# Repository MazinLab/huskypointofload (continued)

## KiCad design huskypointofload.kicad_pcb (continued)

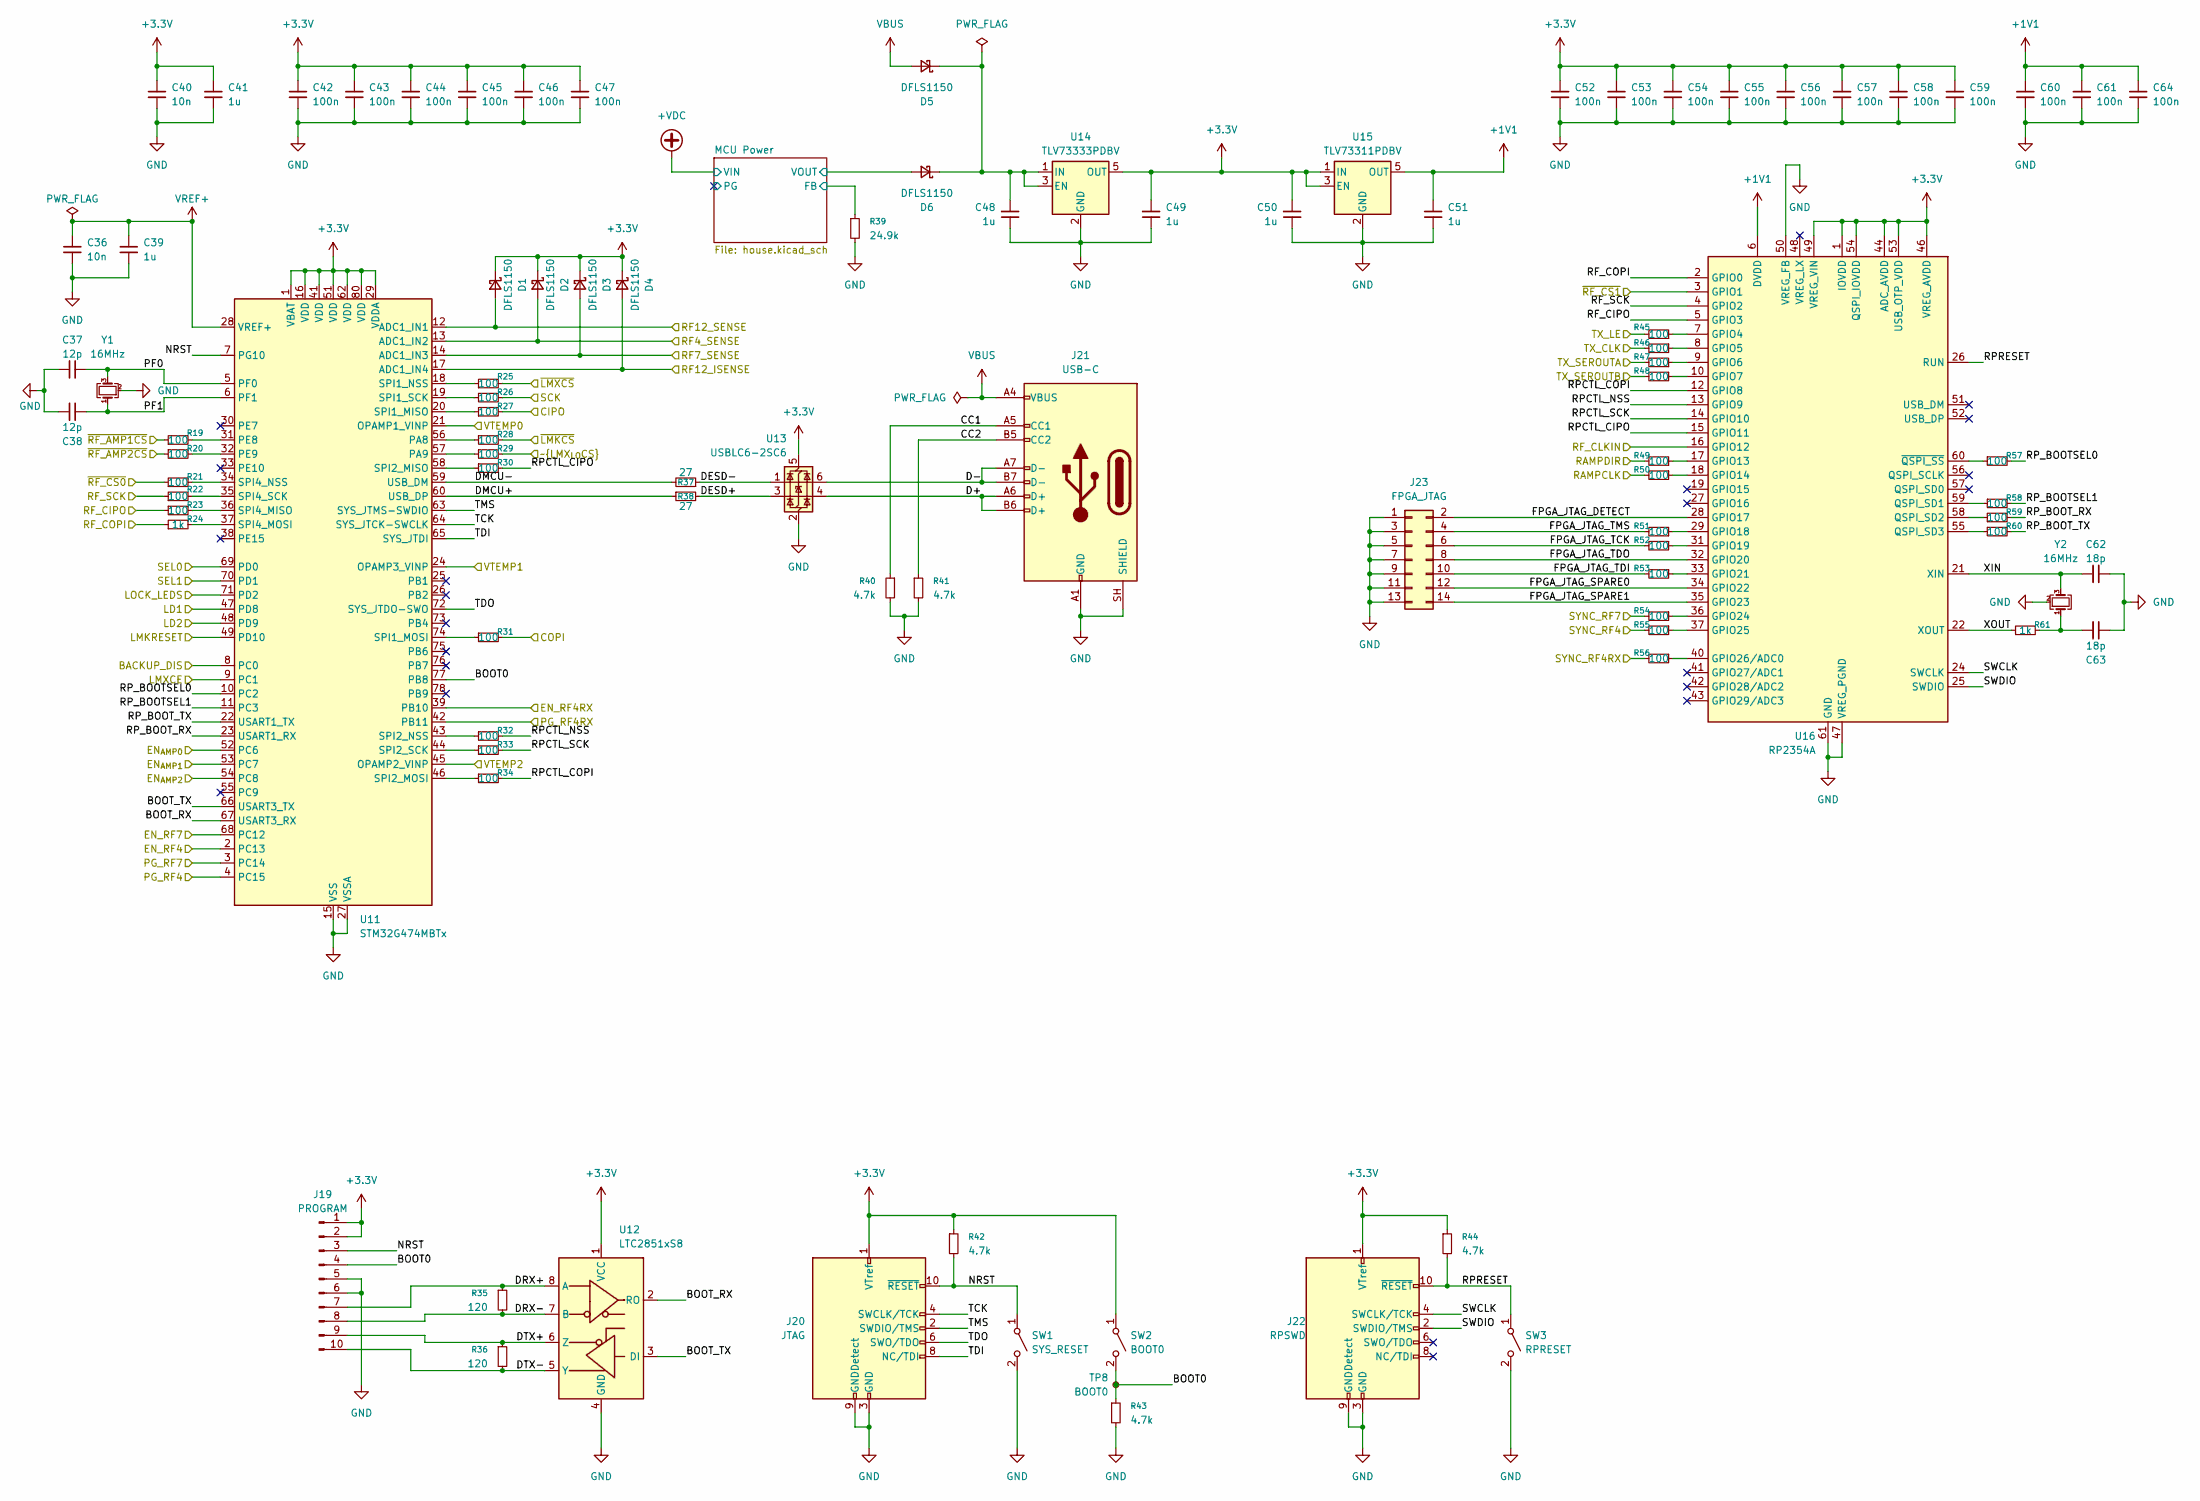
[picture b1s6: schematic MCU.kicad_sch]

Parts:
C36, C40: 10n; C_0402_1005Metric; DIGIKEY_PN 490-6351-1-ND
C37, C38: 12p; C_0402_1005Metric; DIGIKEY_PN 490-11190-1-ND
C39, C41: 1u; C_0402_1005Metric; DIGIKEY_PN 490-13339-1-ND
C42, C43, C44, C45, C46, C47, C52, C53, C54, C55, C56, C57, C58, C59, C60, C61, C64: 100n; C_0402_1005Metric; DIGIKEY_PN 490-14603-1-ND
C48, C49, C50, C51: 1u; C_0402_1005Metric
C62, C63: 18p; C_0402_1005Metric
D1, D2, D3, D4, D5, D6: DFLS1150; D_PowerDI-123; DIGIKEY_PN DFLS1150DICT-ND
J19: PROGRAM; Molex_PicoBlade_53048-1010_1x10_P1.25mm_Horizontal
J20: JTAG; PinHeader_2x05_P1.27mm_Vertical_SMD; DIGIKEY_PN SAM1161-05-ND
J21: USB-C; USB_C_Receptacle_JAE_DX07S016JA1R1500; DIGIKEY_PN 670-DX07S016JA1R1500CT-ND
J22: RPSWD; PinHeader_2x05_P1.27mm_Vertical_SMD; DIGIKEY_PN SAM1161-05-ND
J23: FPGA_JTAG
R19, R20, R21, R22, R23, R25, R26, R27, R28, R29, R30, R31, R32, R33, R34, R45, R46, R47, R48, R49, R50, R51, R52, R53, R54, R55, R56, R57, R58, R59, R60: 100; R_0402_1005Metric
R24, R61: 1k; R_0402_1005Metric
R35, R36: 120; R_0402_1005Metric; DIGIKEY_PN 311-120LRCT-ND
R37, R38: 27; R_0402_1005Metric; DIGIKEY_PN P27.0LCT-ND
R39: 24.9k; R_0402_1005Metric
R40, R41, R42, R43, R44: 4.7k; R_0402_1005Metric; DIGIKEY_PN 311-4.7KJRCT-ND
SW1: SYS_RESET; SW_SPST_PTS810; DIGIKEY_PN CKN10502CT-ND
SW2: BOOT0; SW_SPST_PTS810; DIGIKEY_PN CKN10502CT-ND
SW3: RPRESET; SW_SPST_PTS810; DIGIKEY_PN CKN10502CT-ND
TP8: BOOT0; TestPoint_Keystone_5015_Micro_Mini; DIGIKEY_PN 36-5015CT-ND
U11: STM32G474MBTx; LQFP-80_12x12mm_P0.5mm; DIGIKEY_PN 497-STM32G474MBT6-ND
U12: LTC2851xS8; SOIC-8_3.9x4.9mm_P1.27mm; DIGIKEY_PN LTC2851IMS8#TRPBFCT-ND
U13: USBLC6-2SC6; SOT-23-6; DIGIKEY_PN 4518-USBLC6-2SC6CT-ND
U14: TLV73333PDBV; SOT-23-5
U15: TLV73311PDBV; SOT-23-5
U16: RP2354A; QFN-60-1EP_7x7mm_P0.4mm_EP3.4x3.4mm
Y1, Y2: 16MHz; Crystal_SMD_3225-4Pin_3.2x2.5mm_HandSoldering; DIGIKEY_PN 2151-RH100-16.000-8-2020-TRCT-ND

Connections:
+1V1: C51.1, C60.1, C61.1, C64.1, U15.5 (OUT), U16.6 (DVDD), U16.23 (DVDD), U16.39 (DVDD)
+3.3V: C40.1, C41.1, C42.1, C43.1, C44.1, C45.1, C46.1, C47.1, C49.1, C50.1, C52.1, C53.1, C54.1, C55.1, C56.1, C57.1, C58.1, C59.1, D1.1 (K), D2.1 (K), D3.1 (K), D4.1 (K), J19.1, J19.2, J20.1 (VTref), J22.1 (VTref), R42.1, R44.1, SW2.1 (A), U11.1 (VBAT), U11.16 (VDD), U11.29 (VDDA), U11.41 (VDD), U11.51 (VDD), U11.62 (VDD), U11.80 (VDD), U12.1 (VCC), U13.5 (VBUS), U14.5 (OUT), U15.1 (IN), U15.3 (EN), U16.1 (IOVDD), U16.11 (IOVDD), U16.20 (IOVDD), U16.30 (IOVDD), U16.38 (IOVDD), U16.44 (ADC_AVDD), U16.45 (IOVDD), U16.46 (VREG_AVDD), U16.49 (VREG_VIN), U16.53 (USB_OTP_VDD), U16.54 (QSPI_IOVDD); also elsewhere on the board
/Clocking/BACKUP_DIS: U11.8 (PC0); also elsewhere on the board
/Clocking/LD1: U11.47 (PD8); also elsewhere on the board
/Clocking/LD2: U11.48 (PD9); also elsewhere on the board
/Clocking/LD_LED_ENABLE: U11.71 (PD2); also elsewhere on the board
/Clocking/LMK04828/SEL0: U11.69 (PD0); also elsewhere on the board
/Clocking/LMK04828/SEL1: U11.70 (PD1); also elsewhere on the board
/Clocking/LMKRESET: U11.49 (PD10); also elsewhere on the board
/Clocking/LMXCE: U11.9 (PC1); also elsewhere on the board
/Clocking/MUXOUT: R27.2; also elsewhere on the board
/Clocking/RAMPCLK: R50.2; also elsewhere on the board
/Clocking/RAMPDIR: R49.2; also elsewhere on the board
/Clocking/~LMKCS: R28.2; also elsewhere on the board
/Clocking/~LMXCS: R25.2; also elsewhere on the board
/Clocking/~LMX_{LOCS}: R29.2; also elsewhere on the board
/MCU/BOOT0: J19.4, R43.1, SW2.2 (B), TP8.1 (1_1), U11.77 (PB8)
/MCU/BOOT_RX: U11.67 (USART3_RX), U12.2 (RO)
/MCU/BOOT_TX: U11.66 (USART3_TX), U12.3 (DI)
/MCU/CC1: J21.A5 (CC1), R40.1
/MCU/CC2: J21.B5 (CC2), R41.1
/MCU/D+: J21.A6 (D+), J21.B6 (D+), U13.4 (I/O2)
/MCU/D-: J21.A7 (D-), J21.B7 (D-), U13.6 (I/O1)
/MCU/DESD+: R38.2, U13.3 (I/O2)
/MCU/DESD-: R37.1, U13.1 (I/O1)
/MCU/DMCU+: R38.1, U11.60 (USB_DP)
/MCU/DMCU-: R37.2, U11.59 (USB_DM)
/MCU/DRX+: J19.7, R35.1, U12.8 (A)
/MCU/DRX-: J19.8, R35.2, U12.7 (B)
/MCU/DTX+: J19.9, R36.1, U12.6 (Z)
/MCU/DTX-: J19.10, R36.2, U12.5 (Y)
/MCU/EN_RF4: U11.2 (PC13); also elsewhere on the board
/MCU/EN_RF4RX: U11.39 (PB10); also elsewhere on the board
/MCU/EN_RF7: U11.68 (PC12); also elsewhere on the board
/MCU/EN_{AMP0}: U11.52 (PC6); also elsewhere on the board
/MCU/EN_{AMP1}: U11.53 (PC7); also elsewhere on the board
/MCU/EN_{AMP2}: U11.54 (PC8); also elsewhere on the board
/MCU/FPGA_JTAG_DETECT: J23.2, U16.28 (GPIO17)
/MCU/FPGA_JTAG_SPARE0: J23.12, U16.34 (GPIO22)
/MCU/FPGA_JTAG_SPARE1: J23.14, U16.35 (GPIO23)
/MCU/FPGA_JTAG_TCK: J23.6, R52.2
/MCU/FPGA_JTAG_TDI: J23.10, R53.2
/MCU/FPGA_JTAG_TDO: J23.8, U16.32 (GPIO20)
/MCU/FPGA_JTAG_TMS: J23.4, R51.2
/MCU/MCU Power/FB: R39.1; also elsewhere on the board
/MCU/MCU Power/VOUT: D6.2 (A); also elsewhere on the board
/MCU/NRST: J19.3, J20.10 (~RESET), R42.2, SW1.1 (A), U11.7 (PG10)
/MCU/PF0: C37.2, U11.5 (PF0), Y1.3
/MCU/PF1: C38.2, U11.6 (PF1), Y1.1
/MCU/PG_RF4: U11.4 (PC15); also elsewhere on the board
/MCU/PG_RF4RX: U11.42 (PB11); also elsewhere on the board
/MCU/PG_RF7: U11.3 (PC14); also elsewhere on the board
/MCU/RF4_SENSE: D2.2 (A), U11.13 (ADC1_IN2); also elsewhere on the board
/MCU/RF7_SENSE: D3.2 (A), U11.14 (ADC1_IN3); also elsewhere on the board
/MCU/RF12_ISENSE: D4.2 (A), U11.17 (ADC1_IN4); also elsewhere on the board
/MCU/RF12_SENSE: D1.2 (A), U11.12 (ADC1_IN1); also elsewhere on the board
/MCU/RF_CLKIN: U16.16 (GPIO12); also elsewhere on the board
/MCU/RPCTL_CIPO: R30.2, U16.15 (GPIO11)
/MCU/RPCTL_COPI: R34.2, U16.12 (GPIO8)
/MCU/RPCTL_NSS: R32.2, U16.13 (GPIO9)
/MCU/RPCTL_SCK: R33.2, U16.14 (GPIO10)
/MCU/RPRESET: J22.10 (~RESET), R44.2, SW3.1 (A), U16.26 (RUN)
/MCU/RP_BOOTSEL0: R57.2, U11.10 (PC2)
/MCU/RP_BOOTSEL1: R58.2, U11.11 (PC3)
/MCU/RP_BOOT_RX: R59.2, U11.23 (USART1_RX)
/MCU/RP_BOOT_TX: R60.2, U11.22 (USART1_TX)
/MCU/SWCLK: J22.4 (SWCLK/TCK), U16.24 (SWCLK)
/MCU/SWDIO: J22.2 (SWDIO/TMS), U16.25 (SWDIO)
/MCU/SYNC_RF4: R55.2; also elsewhere on the board
/MCU/SYNC_RF4RX: R56.2; also elsewhere on the board
/MCU/SYNC_RF7: R54.2; also elsewhere on the board
/MCU/TCK: J20.4 (SWCLK/TCK), U11.64 (SYS_JTCK-SWCLK)
/MCU/TDI: J20.8 (NC/TDI), U11.65 (SYS_JTDI)
/MCU/TDO: J20.6 (SWO/TDO), U11.72 (SYS_JTDO-SWO)
/MCU/TMS: J20.2 (SWDIO/TMS), U11.63 (SYS_JTMS-SWDIO)
/MCU/TX_SEROUTA: R47.2; also elsewhere on the board
/MCU/TX_SEROUTB: R48.2; also elsewhere on the board
/MCU/VTEMP0: U11.21 (OPAMP1_VINP); also elsewhere on the board
/MCU/VTEMP1: U11.24 (OPAMP3_VINP); also elsewhere on the board
/MCU/VTEMP2: U11.45 (OPAMP2_VINP); also elsewhere on the board
/MCU/XIN: C62.2, U16.21 (XIN), Y2.3
/MCU/XOUT: R61.1, U16.22 (XOUT)
/RF_CIPO: R23.1, U16.5 (GPIO3); also elsewhere on the board
/RF_COPI: R24.1, U16.2 (GPIO0); also elsewhere on the board
/RF_SCK: R22.1, U16.4 (GPIO2); also elsewhere on the board
/Recieve Chain/CIPO: R31.2; also elsewhere on the board
/Recieve Chain/SCK: R26.2; also elsewhere on the board
/Recieve Chain/~CS_{AMP1}: R19.1; also elsewhere on the board
/Recieve Chain/~CS_{AMP2}: R20.1; also elsewhere on the board
/Transmit Chain/CLK: R46.2; also elsewhere on the board
/Transmit Chain/LE: R45.2; also elsewhere on the board
/~RF_CS0: R21.1; also elsewhere on the board
/~RF_CS1: U16.3 (GPIO1); also elsewhere on the board
GND: C36.2, C37.1, C38.1, C39.2, C40.2, C41.2, C42.2, C43.2, C44.2, C45.2, C46.2, C47.2, C48.2, C49.2, C50.2, C51.2, C52.2, C53.2, C54.2, C55.2, C56.2, C57.2, C58.2, C59.2, C60.2, C61.2, C62.1, C63.1, C64.2, J19.5, J19.6, J20.3 (GND), J20.5 (GND), J20.9 (GNDDetect), J21.A1 (GND), J21.A12 (GND), J21.B1 (GND), J21.B12 (GND), J21.SH (SHIELD), J22.3 (GND), J22.5 (GND), J22.9 (GNDDetect), J23.1, J23.3, J23.5, J23.7, J23.9, J23.11, J23.13, R39.2, R40.2, R41.2, R43.2, SW1.2 (B), SW3.2 (B), U11.15 (VSS), U11.27 (VSSA), U11.40 (VSS), U11.50 (VSS), U11.61 (VSS), U11.79 (VSS), U12.4 (GND), U13.2 (GND), U14.2 (GND), U15.2 (GND), U16.47 (VREG_PGND), U16.50 (VREG_FB), U16.61 (GND), Y1.2 (G), Y1.4 (G), Y2.2 (G), Y2.4 (G); also elsewhere on the board
unnamed: C63.2, R61.2, Y2.1
unnamed: C48.1, D5.1 (K), D6.1 (K), U14.1 (IN), U14.3 (EN)
unnamed: R25.1, U11.18 (SPI1_NSS)
unnamed: R26.1, U11.19 (SPI1_SCK)
unnamed: R27.1, U11.20 (SPI1_MISO)
unnamed: R28.1, U11.56 (PA8)
unnamed: R29.1, U11.57 (PA9)
unnamed: R30.1, U11.58 (SPI2_MISO)
unnamed: R31.1, U11.74 (SPI1_MOSI)
unnamed: R32.1, U11.43 (SPI2_NSS)
unnamed: R33.1, U11.44 (SPI2_SCK)
unnamed: R34.1, U11.46 (SPI2_MOSI)
unnamed: R19.2, U11.31 (PE8)
unnamed: R20.2, U11.32 (PE9)
unnamed: R21.2, U11.34 (SPI4_NSS)
unnamed: R22.2, U11.35 (SPI4_SCK)
unnamed: R23.2, U11.36 (SPI4_MISO)
unnamed: R24.2, U11.37 (SPI4_MOSI)
unnamed: R45.1, U16.7 (GPIO4)
unnamed: R46.1, U16.8 (GPIO5)
unnamed: R47.1, U16.9 (GPIO6)
unnamed: R48.1, U16.10 (GPIO7)
unnamed: R49.1, U16.17 (GPIO13)
unnamed: R50.1, U16.18 (GPIO14)
unnamed: R51.1, U16.29 (GPIO18)
unnamed: R52.1, U16.31 (GPIO19)
unnamed: R53.1, U16.33 (GPIO21)
unnamed: R54.1, U16.36 (GPIO24)
unnamed: R55.1, U16.37 (GPIO25)
unnamed: R56.1, U16.40 (GPIO26/ADC0)
unnamed: R58.1, U16.59 (QSPI_SD1)
unnamed: R59.1, U16.58 (QSPI_SD2)
unnamed: R60.1, U16.55 (QSPI_SD3)
unnamed: R57.1, U16.60 (~QSPI_SS)
VBUS: D5.2 (A), J21.A4 (VBUS), J21.A9 (VBUS), J21.B4 (VBUS), J21.B9 (VBUS)
VREF+: C36.1, C39.1, U11.28 (VREF+)

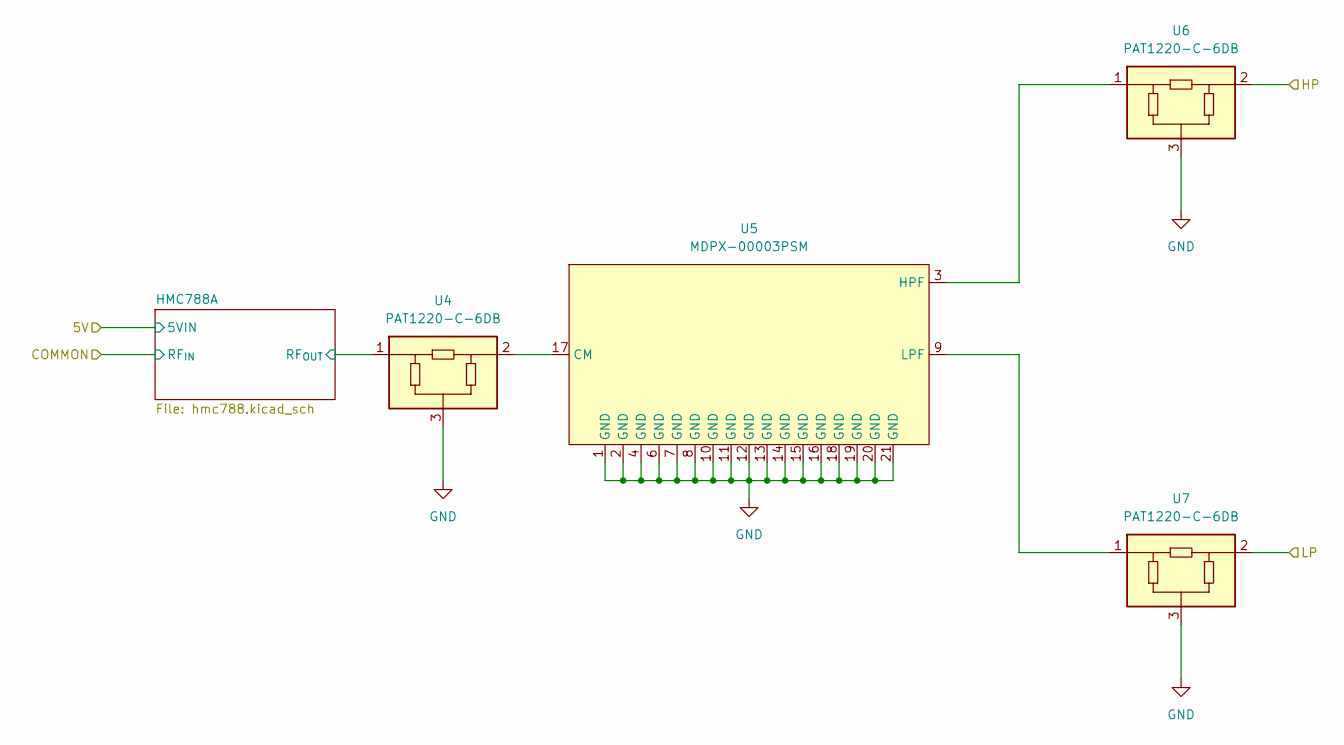
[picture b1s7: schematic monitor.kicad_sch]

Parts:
U4, U6, U7: PAT1220-C-6DB; RF_Attenuator_Susumu_PAT1220
U5: MDPX-00003PSM; VQFN-24-1EP_4x4mm_P0.5mm_EP2.45x2.45mm

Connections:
/Monitor Path/HMC788A/RF_{OUT}: U4.1; also elsewhere on the board
/Monitor Path/HP: U6.2; also elsewhere on the board
/Monitor Path/LP: U7.2; also elsewhere on the board
GND: U4.3, U5.1 (GND), U5.2 (GND), U5.4 (GND), U5.6 (GND), U5.7 (GND), U5.8 (GND), U5.10 (GND), U5.11 (GND), U5.12 (GND), U5.13 (GND), U5.14 (GND), U5.15 (GND), U5.16 (GND), U5.18 (GND), U5.19 (GND), U5.20 (GND), U5.21 (GND), U6.3, U7.3; also elsewhere on the board
unnamed: U4.2, U5.17 (CM)
unnamed: U5.3 (HPF), U6.1
unnamed: U5.9 (LPF), U7.1

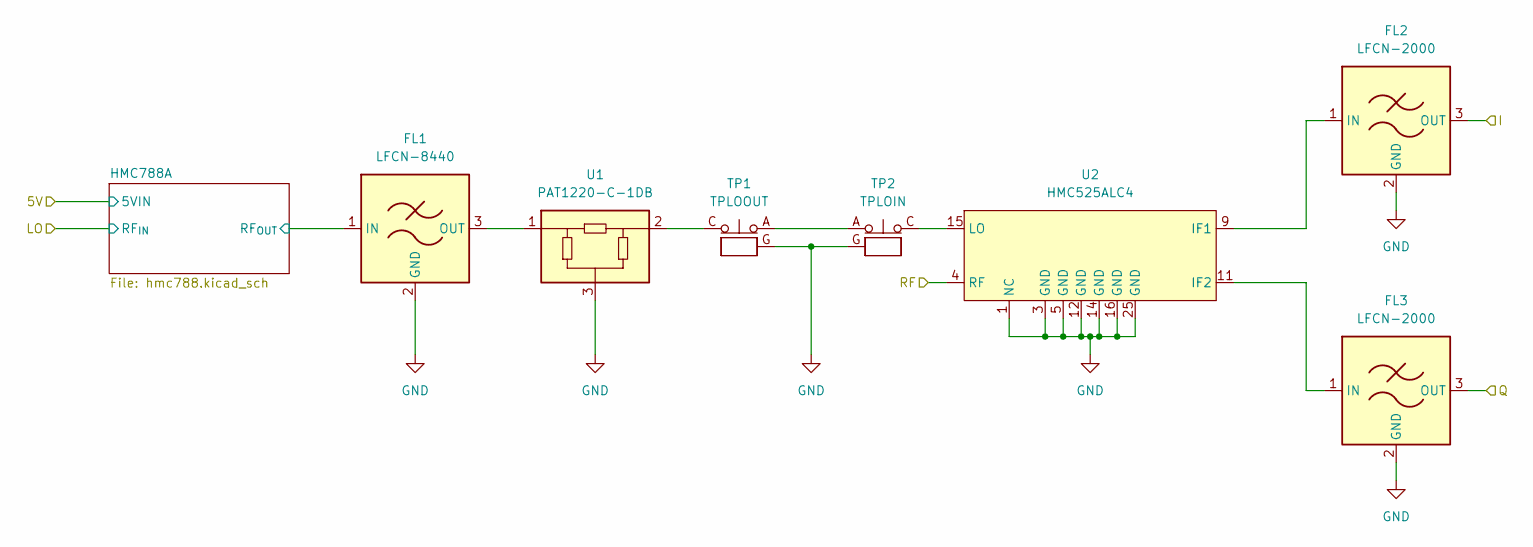
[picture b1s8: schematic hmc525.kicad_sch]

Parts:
FL1: LFCN-8440; Filter_Mini-Circuits_FV1206-4
FL2, FL3: LFCN-2000; Filter_Mini-Circuits_FV1206
TP1: TPLOOUT; CoaxialSwitch_Hirose_MS-156C3_Horizontal
TP2: TPLOIN; CoaxialSwitch_Hirose_MS-156C3_Horizontal
U1: PAT1220-C-1DB; RF_Attenuator_Susumu_PAT1220
U2: HMC525ALC4; QFN-24-1EP_4x4mm_P0.5mm_EP2.5x2.5mm

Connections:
/TX Mixer/HMC788A/RF_{OUT}: FL1.1 (IN); also elsewhere on the board
/TX Mixer/I: FL2.3 (OUT); also elsewhere on the board
/TX Mixer/Q: FL3.3 (OUT); also elsewhere on the board
/TX Mixer/RF: U2.4 (RF); also elsewhere on the board
GND: FL1.2 (GND), FL1.4 (GND), FL2.2 (GND), FL2.4 (GND), FL3.2 (GND), FL3.4 (GND), TP1.G, TP2.G, U1.3, U2.1 (NC), U2.2 (NC), U2.3 (GND), U2.5 (GND), U2.6 (NC), U2.7 (NC), U2.8 (NC), U2.10 (NC), U2.12 (GND), U2.13 (NC), U2.14 (GND), U2.16 (GND), U2.17 (NC), U2.18 (NC), U2.19 (NC), U2.20 (NC), U2.21 (NC), U2.22 (NC), U2.23 (NC), U2.24 (NC), U2.25 (GND); also elsewhere on the board
unnamed: FL1.3 (OUT), U1.1
unnamed: FL2.1 (IN), U2.9 (IF1)
unnamed: FL3.1 (IN), U2.11 (IF2)
unnamed: TP1.A, TP2.A
unnamed: TP1.C, U1.2
unnamed: TP2.C, U2.15 (LO)

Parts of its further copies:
FL4: LFCN-8440; Filter_Mini-Circuits_FV1206-4
FL5, FL6: LFCN-2000; Filter_Mini-Circuits_FV1206
TP19: TPLOOUT; CoaxialSwitch_Hirose_MS-156C3_Horizontal
TP20: TPLOIN; CoaxialSwitch_Hirose_MS-156C3_Horizontal
U42: PAT1220-C-1DB; RF_Attenuator_Susumu_PAT1220
U43: HMC525ALC4; QFN-24-1EP_4x4mm_P0.5mm_EP2.5x2.5mm

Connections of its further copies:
/RX Mixer/HMC788A/RF_{OUT}: FL4.1 (IN); also elsewhere on the board
/RX Mixer/I: FL5.3 (OUT); also elsewhere on the board
/RX Mixer/Q: FL6.3 (OUT); also elsewhere on the board
/RX Mixer/RF: U43.4 (RF); also elsewhere on the board
GND: FL4.2 (GND), FL4.4 (GND), FL5.2 (GND), FL5.4 (GND), FL6.2 (GND), FL6.4 (GND), TP19.G, TP20.G, U42.3, U43.1 (NC), U43.2 (NC), U43.3 (GND), U43.5 (GND), U43.6 (NC), U43.7 (NC), U43.8 (NC), U43.10 (NC), U43.12 (GND), U43.13 (NC), U43.14 (GND), U43.16 (GND), U43.17 (NC), U43.18 (NC), U43.19 (NC), U43.20 (NC), U43.21 (NC), U43.22 (NC), U43.23 (NC), U43.24 (NC), U43.25 (GND); also elsewhere on the board
unnamed: FL4.3 (OUT), U42.1
unnamed: FL5.1 (IN), U43.9 (IF1)
unnamed: FL6.1 (IN), U43.11 (IF2)
unnamed: TP19.A, TP20.A
unnamed: TP19.C, U42.2
unnamed: TP20.C, U43.15 (LO)

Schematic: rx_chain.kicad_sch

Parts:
C172, C174: 1u; C_0402_1005Metric
C173, C305: 1n; C_0201_0603Metric
C175, C178, C179, C180, C181, C184, C185, C186, C187: 1u; NFM18PS; DIGIKEY_PN 490-13394-1-ND
C176, C182: 10u; C_0603_1608Metric; DIGIKEY_PN 490-10727-1-ND; not fitted
C177, C183: 4.7u; C_1206_3216Metric; DIGIKEY_PN 490-GRM31CZ72A475ME11LCT-ND; not fitted
R202, R207, R213: 453k; R_0402_1005Metric; DIGIKEY_PN 13-RC0402FR-13453KLCT-ND
R203, R208, R214: 33k; R_0402_1005Metric; DIGIKEY_PN YAG4374CT-ND
R204: 357k; R_0402_1005Metric; DIGIKEY_PN YAG3129CT-ND
R205: 40k; R_0402_1005Metric; DIGIKEY_PN 738-RNCF0402BTE40K0CT-ND
R206: 1.54k; R_0402_1005Metric
R209, R210, R211, R212, R215, R216, R217, R218: 0; R_0402_1005Metric
R275: 100; R_0402_1005Metric
TP10: TPG; TestPoint_Pad_D4.0mm
TP11: TPRXIN; CoaxialSwitch_Hirose_MS-156C3_Horizontal
U26: TLV73333PDBV; SOT-23-5
U27: ADL8124; QFN-8_EP_2x2_Pitch0.5mm_ADL8124
U28: ADL6332; LGA-24_CC-24-17
U29: ADL6331; LGA-24_CC-24-17
U30: MEQ0-20ASM
U31: MC16-0222SM; VQFN-24-1EP_4x4mm_P0.5mm_EP2.45x2.45mm

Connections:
/Clocking/MUXOUT: U28.19 (SDIO), U29.19 (SDIO); also elsewhere on the board
/MCU/EN_{AMP0}: U27.7 (EN); also elsewhere on the board
/MCU/EN_{AMP1}: U28.12 (EN); also elsewhere on the board
/MCU/EN_{AMP2}: U29.12 (EN); also elsewhere on the board
/MCU/VTEMP0: U27.2 (VTEMP); also elsewhere on the board
/MCU/VTEMP1: U28.7 (MUXOUT); also elsewhere on the board
/MCU/VTEMP2: U29.7 (MUXOUT); also elsewhere on the board
/Monitor Path/COMMON: U31.1 (-16dB); also elsewhere on the board
/RX Mixer/RF: TP11.C; also elsewhere on the board
/Recieve Chain/+3.3VA_LNA: C175.3, R206.1, U27.8 (VDD)
/Recieve Chain/+4V_RX: C172.1, R204.1, U26.1 (IN), U26.3 (EN); also elsewhere on the board
/Recieve Chain/CIPO: R275.2, U29.18 (SDO); also elsewhere on the board
/Recieve Chain/Linear POL AMP1/PGFB: R207.2; also elsewhere on the board
/Recieve Chain/Linear POL AMP1/SET: R208.1; also elsewhere on the board
/Recieve Chain/Linear POL LMK AMP2/PGFB: R213.2; also elsewhere on the board
/Recieve Chain/Linear POL LMK AMP2/SET: R214.1; also elsewhere on the board
/Recieve Chain/Linear POL LMK VCO/KELVIN: C175.1, R202.1; also elsewhere on the board
/Recieve Chain/Linear POL LMK VCO/PGFB: R202.2; also elsewhere on the board
/Recieve Chain/Linear POL LMK VCO/SET: R203.1; also elsewhere on the board
/Recieve Chain/RF Switching PSU/PGFB-: R204.2; also elsewhere on the board
/Recieve Chain/RF Switching PSU/SET: R205.1; also elsewhere on the board
/Recieve Chain/RFIN: C173.2; also elsewhere on the board
/Recieve Chain/SCK: U28.20 (SCLK), U29.20 (SCLK); also elsewhere on the board
/Recieve Chain/VCC_AMP1: C176.1, C177.1, R207.1, R209.1, R210.1, R211.1, R212.1; also elsewhere on the board
/Recieve Chain/VCC_AMP1_AMP1: C178.3, U28.8 (VCC_{AMP1A})
/Recieve Chain/VCC_AMP1_AMP1A: C179.3, U28.9 (VCC_{AMP1})
/Recieve Chain/VCC_AMP1_AMP2: C180.3, U28.10 (VCC_{AMP2A})
/Recieve Chain/VCC_AMP1_AMP2A: C181.3, U28.11 (VCC_{AMP2})
/Recieve Chain/VCC_AMP2: C182.1, C183.1, R213.1, R215.1, R216.1, R217.1, R218.1; also elsewhere on the board
/Recieve Chain/VCC_AMP2_AMP1: C184.3, U29.8 (VCC_{AMP1A})
/Recieve Chain/VCC_AMP2_AMP1A: C185.3, U29.9 (VCC_{AMP1})
/Recieve Chain/VCC_AMP2_AMP2: C186.3, U29.10 (VCC_{AMP2A})
/Recieve Chain/VCC_AMP2_AMP2A: C187.3, U29.11 (VCC_{AMP2})
/Recieve Chain/VCC_RX_DIG: C174.1, U26.5 (OUT), U28.22 (VCC_{FUSE}), U29.22 (VCC_{FUSE})
/Recieve Chain/~CS_{AMP1}: U28.21 (~CS); also elsewhere on the board
/Recieve Chain/~CS_{AMP2}: U29.21 (~CS); also elsewhere on the board
GND: C172.2, C174.2, C175.2, C176.2, C177.2, C178.2, C179.2, C180.2, C181.2, C182.2, C183.2, C184.2, C185.2, C186.2, C187.2, R203.2, R205.2, R208.2, R214.2, TP10.1 (1_1), TP11.G, U26.2 (GND), U27.3 (GND), U27.6 (GND), U27.9 (GND), U28.1 (CA2), U28.2 (GND), U28.4 (GND), U28.5 (GND), U28.6 (ATT1), U28.13 (ATT0), U28.14 (GND), U28.17 (GND), U28.23 (CA0), U28.24 (CA1), U28.25 (GND), U29.1 (CA2), U29.2 (GND), U29.5 (GND), U29.6 (ATT1), U29.13 (ATT0), U29.14 (GND), U29.16 (GND), U29.17 (GND), U29.23 (CA0), U29.24 (CA1), U29.25 (GND), U30.2 (GND), U30.3 (GND), U30.4 (GND), U30.5 (GND), U30.6 (GND), U30.7 (GND), U30.8 (GND), U30.10 (GND), U30.11 (GND), U30.12 (GND), U30.13 (GND), U31.2 (GND), U31.3 (GND), U31.4 (GND), U31.6 (GND), U31.7 (GND), U31.8 (GND), U31.10 (GND), U31.12 (GND), U31.13 (GND), U31.14 (GND), U31.15 (GND), U31.16 (GND), U31.17 (GND), U31.18 (GND), U31.19 (GND), U31.20 (GND), U31.21 (GND); also elsewhere on the board
unnamed: C178.1, R209.2
unnamed: C179.1, R210.2
unnamed: C180.1, R211.2
unnamed: C181.1, R212.2
unnamed: C184.1, R215.2
unnamed: C185.1, R216.2
unnamed: C186.1, R217.2
unnamed: C187.1, R218.2
unnamed: R206.2, U27.1 (RBIAS)
unnamed: C173.1, U27.4 (RF_{IN})
unnamed: U27.5 (RF_{OUT}), U28.3 (RFIN)
unnamed: U28.15 (RFOUT_{N}), U29.4 (RFIN_{N})
unnamed: U28.16 (RFOUT_{P}), U29.3 (RFIN_{P})
unnamed: R275.1, U28.18 (SDO)
unnamed: U29.15 (RFOUT), U30.1 (RFIN)
unnamed: C305.2, U30.9 (RFOUT)
unnamed: C305.1, U31.5 (RFIN)
unnamed: TP11.A, U31.11 (RFOUT)

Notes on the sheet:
For Solderin Coax Probe
NOTE: Use LT3042 not 3045 for purposes of purchasing and assembly!

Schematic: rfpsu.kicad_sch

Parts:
C13, C14, C15, C16: 22u; C_1206_3216Metric; DIGIKEY_PN 490-GRM31CC71E226ME15LCT-ND
C17, C18, C19, C21: 2.2u; C_0603_1608Metric; DIGIKEY_PN 490-12732-1-ND
C20: 1u; C_0402_1005Metric; DIGIKEY_PN 490-14409-1-ND
C22: 10n; C_0402_1005Metric; DIGIKEY_PN 490-6351-1-ND
C23: 82p; C_0402_1005Metric; DIGIKEY_PN 490-GCM1555C1H820JA16DCT-ND
C24: 100n; C_0402_1005Metric; DIGIKEY_PN 490-14603-1-ND
C26, C28: 2.2u; C_0201_0603Metric; DIGIKEY_PN 490-GRM033R60J225ME01DCT-ND
C27: 22u; C_0402_1005Metric; DIGIKEY_PN 490-GRM155R60J226ME11DCT-ND
C29, C30: 10u; NFM18PC; DIGIKEY_PN 490-NFM18PC106D0J3LCT-ND
C31: 100u; C_0805_2012Metric; DIGIKEY_PN 490-13981-1-ND
C32, C33, C34: DNP; C_0402_1005Metric; not fitted
C35: 1n; C_0402_1005Metric
J18: VSENSE; SMA_Amphenol_132134-10_Vertical; DIGIKEY_PN ARF2755-ND
L1: 1u; L_Bourns_SRP5030T; DIGIKEY_PN SRP5030T-1R0MCT-ND
L2: 220n; L_Bourns_SRP7028A_7.3x6.6mm; DIGIKEY_PN 118-SRP7028AA-R22MCT-ND
R14: 4.7k; R_0402_1005Metric; DIGIKEY_PN 311-4.7KJRCT-ND
R15: 499; R_0402_1005Metric; DIGIKEY_PN 311-499LRCT-ND
R16: 2.2; R_0402_1005Metric; DIGIKEY_PN YAG3471CT-ND
R17: 47.5k; R_0402_1005Metric; DIGIKEY_PN YAG4390CT-ND
R18: 49.9k; R_0402_1005Metric; DIGIKEY_PN YAG4394CT-ND
TP3: INTVCC; TestPoint_Keystone_5015_Micro_Mini; DIGIKEY_PN 36-5015CT-ND
TP4: VC; TestPoint_Keystone_5015_Micro_Mini; DIGIKEY_PN 36-5015CT-ND
TP5: CLKOUT; TestPoint_Keystone_5015_Micro_Mini; DIGIKEY_PN 36-5015CT-ND
TP6: PHMODE; TestPoint_Keystone_5015_Micro_Mini; DIGIKEY_PN 36-5015CT-ND
TP7: LNSW; TestPoint_Keystone_5015_Micro_Mini; DIGIKEY_PN 36-5015CT-ND
U10: LT8625S; QFN-20-1EP_3x4mm_P0.5mm_EP1.65x2.65mm; DIGIKEY_PN 505-LT8625SIV#TRMPBFCT-ND

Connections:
+4V: C30.3, C31.1, C32.1, C33.2, C34.1, C34.2, J18.1 (In), U10.13 (OUTS); also elsewhere on the board
+12V_RF: C13.1, C14.1, C15.1, C16.1, C17.1, C18.1, C19.1, C21.1, R16.2, U10.5 (PVIN), U10.6 (PVIN), U10.23 (NC); also elsewhere on the board
/MCU/EN_RF4: R14.1, U10.8 (EN); also elsewhere on the board
/MCU/PG_RF4: U10.16 (PG); also elsewhere on the board
/MCU/SYNC_RF4: U10.17 (SYNC); also elsewhere on the board
/RF Supplies/RF Switching PSU/INTVCC: C20.1, TP3.1 (1_1), U10.9 (INTVCC)
/RF Supplies/RF Switching PSU/PGFB-: C35.1, R18.1, U10.14 (PGFB); also elsewhere on the board
/RF Supplies/RF Switching PSU/SET: C26.1, U10.11 (SET); also elsewhere on the board
GND: C13.2, C14.2, C15.2, C16.2, C17.2, C18.2, C19.2, C20.2, C21.2, C22.2, C23.2, C24.2, C26.2, C27.2, C28.2, C29.2, C30.2, C31.2, C32.2, C33.1, C35.2, J18.2 (Ext), R14.2, R17.2, R18.2, U10.3 (GND), U10.4 (GND), U10.21 (GND); also elsewhere on the board
unnamed: C22.1, R15.2
unnamed: C27.1, C28.1, C29.1, L1.2
unnamed: C29.3, L2.1
unnamed: C30.1, L2.2
unnamed: L1.1, TP7.1 (1_1), U10.1 (SW), U10.20 (SW), U10.22 (NC)
unnamed: TP5.1 (1_1), U10.18 (CLKOUT)
unnamed: TP6.1 (1_1), U10.10 (PHMODE)
unnamed: R17.1, U10.15 (RT)
unnamed: C24.1, R16.1, U10.7 (SVIN)
unnamed: C23.1, R15.1, TP4.1 (1_1), U10.12 (VC)

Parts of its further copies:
C247, C248, C249, C250, C282, C283, C284, C285: 22u; C_1206_3216Metric; DIGIKEY_PN 490-GRM31CC71E226ME15LCT-ND
C251, C252, C253, C255, C286, C287, C288, C290: 2.2u; C_0603_1608Metric; DIGIKEY_PN 490-12732-1-ND
C254, C289: 1u; C_0402_1005Metric; DIGIKEY_PN 490-14409-1-ND
C256, C291: 10n; C_0402_1005Metric; DIGIKEY_PN 490-6351-1-ND
C257, C292: 82p; C_0402_1005Metric; DIGIKEY_PN 490-GCM1555C1H820JA16DCT-ND
C258, C293: 100n; C_0402_1005Metric; DIGIKEY_PN 490-14603-1-ND
C260, C262, C295, C297: 2.2u; C_0201_0603Metric; DIGIKEY_PN 490-GRM033R60J225ME01DCT-ND
C261, C296: 22u; C_0402_1005Metric; DIGIKEY_PN 490-GRM155R60J226ME11DCT-ND
C263, C264, C298, C299: 10u; NFM18PC; DIGIKEY_PN 490-NFM18PC106D0J3LCT-ND
C265, C300: 100u; C_0805_2012Metric; DIGIKEY_PN 490-13981-1-ND
C266, C267, C268, C301, C302, C303: DNP; C_0402_1005Metric; not fitted
C269, C304: 1n; C_0402_1005Metric
J43, J46: VSENSE; SMA_Amphenol_132134-10_Vertical; DIGIKEY_PN ARF2755-ND
L8, L10: 1u; L_Bourns_SRP5030T; DIGIKEY_PN SRP5030T-1R0MCT-ND
L9, L11: 220n; L_Bourns_SRP7028A_7.3x6.6mm; DIGIKEY_PN 118-SRP7028AA-R22MCT-ND
R259, R270: 4.7k; R_0402_1005Metric; DIGIKEY_PN 311-4.7KJRCT-ND
R260, R271: 499; R_0402_1005Metric; DIGIKEY_PN 311-499LRCT-ND
R261, R272: 2.2; R_0402_1005Metric; DIGIKEY_PN YAG3471CT-ND
R262, R273: 47.5k; R_0402_1005Metric; DIGIKEY_PN YAG4390CT-ND
R263, R274: 49.9k; R_0402_1005Metric; DIGIKEY_PN YAG4394CT-ND
TP14, TP21: INTVCC; TestPoint_Keystone_5015_Micro_Mini; DIGIKEY_PN 36-5015CT-ND
TP15, TP22: VC; TestPoint_Keystone_5015_Micro_Mini; DIGIKEY_PN 36-5015CT-ND
TP16, TP23: CLKOUT; TestPoint_Keystone_5015_Micro_Mini; DIGIKEY_PN 36-5015CT-ND
TP17, TP24: PHMODE; TestPoint_Keystone_5015_Micro_Mini; DIGIKEY_PN 36-5015CT-ND
TP18, TP25: LNSW; TestPoint_Keystone_5015_Micro_Mini; DIGIKEY_PN 36-5015CT-ND
U40, U46: LT8625S; QFN-20-1EP_3x4mm_P0.5mm_EP1.65x2.65mm; DIGIKEY_PN 505-LT8625SIV#TRMPBFCT-ND

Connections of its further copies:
+7V: C264.3, C265.1, C266.1, C268.2, J43.1 (In); also elsewhere on the board
+12V_RF: C247.1, C248.1, C249.1, C250.1, C251.1, C252.1, C253.1, C255.1, C282.1, C283.1, C284.1, C285.1, C286.1, C287.1, C288.1, C290.1, R261.2, R272.2, U40.5 (PVIN), U40.6 (PVIN), U40.23 (NC), U46.5 (PVIN), U46.6 (PVIN), U46.23 (NC); also elsewhere on the board
/MCU/EN_RF4RX: R270.1, U46.8 (EN); also elsewhere on the board
/MCU/EN_RF7: R259.1, U40.8 (EN); also elsewhere on the board
/MCU/PG_RF4RX: U46.16 (PG); also elsewhere on the board
/MCU/PG_RF7: U40.16 (PG); also elsewhere on the board
/MCU/SYNC_RF4RX: U46.17 (SYNC); also elsewhere on the board
/MCU/SYNC_RF7: U40.17 (SYNC); also elsewhere on the board
/RF Supplies/RF Switching 7V/INTVCC: C254.1, TP14.1 (1_1), U40.9 (INTVCC)
/RF Supplies/RF Switching 7V/OUTS: C267.2, C268.1, U40.13 (OUTS); also elsewhere on the board
/RF Supplies/RF Switching 7V/PGFB-: C269.1, R263.1, U40.14 (PGFB); also elsewhere on the board
/RF Supplies/RF Switching 7V/SET: C260.1, U40.11 (SET); also elsewhere on the board
/Recieve Chain/+4V_RX: C299.3, C300.1, C301.1, C302.2, C303.1, C303.2, J46.1 (In), U46.13 (OUTS); also elsewhere on the board
/Recieve Chain/RF Switching PSU/INTVCC: C289.1, TP21.1 (1_1), U46.9 (INTVCC)
/Recieve Chain/RF Switching PSU/PGFB-: C304.1, R274.1, U46.14 (PGFB); also elsewhere on the board
/Recieve Chain/RF Switching PSU/SET: C295.1, U46.11 (SET); also elsewhere on the board
GND: C247.2, C248.2, C249.2, C250.2, C251.2, C252.2, C253.2, C254.2, C255.2, C256.2, C257.2, C258.2, C260.2, C261.2, C262.2, C263.2, C264.2, C265.2, C266.2, C267.1, C269.2, C282.2, C283.2, C284.2, C285.2, C286.2, C287.2, C288.2, C289.2, C290.2, C291.2, C292.2, C293.2, C295.2, C296.2, C297.2, C298.2, C299.2, C300.2, C301.2, C302.1, C304.2, J43.2 (Ext), J46.2 (Ext), R259.2, R262.2, R263.2, R270.2, R273.2, R274.2, U40.3 (GND), U40.4 (GND), U40.21 (GND), U46.3 (GND), U46.4 (GND), U46.21 (GND); also elsewhere on the board
unnamed: C256.1, R260.2
unnamed: C261.1, C262.1, C263.1, L8.2
unnamed: C263.3, L9.1
unnamed: C264.1, L9.2
unnamed: C291.1, R271.2
unnamed: C296.1, C297.1, C298.1, L10.2
unnamed: C298.3, L11.1
unnamed: C299.1, L11.2
unnamed: L8.1, TP18.1 (1_1), U40.1 (SW), U40.20 (SW), U40.22 (NC)
unnamed: L10.1, TP25.1 (1_1), U46.1 (SW), U46.20 (SW), U46.22 (NC)
unnamed: TP16.1 (1_1), U40.18 (CLKOUT)
unnamed: TP17.1 (1_1), U40.10 (PHMODE)
unnamed: R262.1, U40.15 (RT)
unnamed: C258.1, R261.1, U40.7 (SVIN)
unnamed: C257.1, R260.1, TP15.1 (1_1), U40.12 (VC)
unnamed: TP23.1 (1_1), U46.18 (CLKOUT)
unnamed: TP24.1 (1_1), U46.10 (PHMODE)
unnamed: R273.1, U46.15 (RT)
unnamed: C293.1, R272.1, U46.7 (SVIN)
unnamed: C292.1, R271.1, TP22.1 (1_1), U46.12 (VC)

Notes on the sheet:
0.22uH 34A ISAT SRP7028AA-R22M
2.2u 6.3V 0201 X5R GRM033R60J225ME01
100u 6.3V 0805 X5R GRM21BR60J107ME15L
2.2u 25V 0603 X7S GRM188C71E225KE11D
1uH 11A ISAT SRP5030T-1R0M
22u 25V 1206 X7S GRM31CC71E226ME15L
10u 6.3V 0603 X5R NFM18PC106D0J3L
22u 6.3V 0402 X5R GRM155R60J226ME11D

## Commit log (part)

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2025-10-30 Add initial schematic for power
2025-10-30 Add SCH PDF
2025-10-30 Fix typo add bom
2025-10-31 Add PCB
2025-11-01 reorg and add 10MHz
2025-11-03 Renumber refdes
2025-11-06 Add lmk and bump schematic size
2025-11-06 Complete LMK schematic
2026-01-06 Add LMX Draft
2026-01-07 Different Matching Circuit
2026-01-08 Add mixer
2026-01-09 WIP Splitrail
2026-01-15 Add VVA Bias generator
